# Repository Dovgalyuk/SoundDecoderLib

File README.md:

# Maple RailRoad Sound Decoder

WiFi controller, sound decoder, and sound projects for model trains.

Project includes library for programming the sounds with set of state machines.

There are several ready-to-use sample sound projects.

# Project structure

* esp32 - directory where building of the firmware starts
* hardware - several versions of PCBs for manufacturing the decoder
* projects - ready-to-use sound projects for different locomotives
* compiler - compiler for the sound projects
* emulator - cab emulator for listening sounds with virtual locomotive control
* sample - dummy player which generates wav file by interpreting the sound project
* other directories include the source code of the firmware

# Bringing locomotive to life

* Get the hardware (order PCB, solder the components)
* Build firmware
  * Install ESP32 toolkit (esp idf)
  * Run esp32/build32M.sh (or other version)
* Upload esp32/build32M/esp32sounddecoder.bin into the ESP32 module
* Build selected sound project with compiler/compiler.py
* Upload built project through the web interface into the controller
* Install the controller into the locomotive

# Software features

Controller provides web interface that may be accessed through
WiFi (default address 192.168.4.1).

Sound module plays 8- or 16-bit sounds in 8 channels.

Output functions and sound schemes are programmed with
custom language. The scripts may include conditions,
loops, and finite state machines. These features
may be used for creating complex sound projects.

# Hardware

Controller is intended to be used with G-scale locomotives
with lithium batteries installed, but it may also be used
with track power (some power capacitors are probably needed).

Controller includes the following hardware components:
* ESP32 CPU with embedded WiFi module and flash memory
* Motor driver
* I2S audio power amplifier (MAX98357A)
* 7 programmable outputs
* BEMF for adjusting the motor speed (work in progress)

# Roadmap

* BEMF with new motor driver
* Support of logical input/outputs
* H0-compatible PCB

# Links

* Radio-controlled engines with sound
  - https://github.com/TheDIYGuy999/Rc_Engine_Sound_ESP32
* Cost effective DIY DCC Decoder for model railroad locomotives
  - https://github.com/gab-k/RP2040-Decoder
* NIMRS: open-source NIMRS-21Pin-Decoder, based on the ESP32-S3 microcontroller
  - https://github.com/CDFER/NIMRS-21Pin-Decoder
  - https://github.com/ProjectInitiative/NIMRS-Firmware

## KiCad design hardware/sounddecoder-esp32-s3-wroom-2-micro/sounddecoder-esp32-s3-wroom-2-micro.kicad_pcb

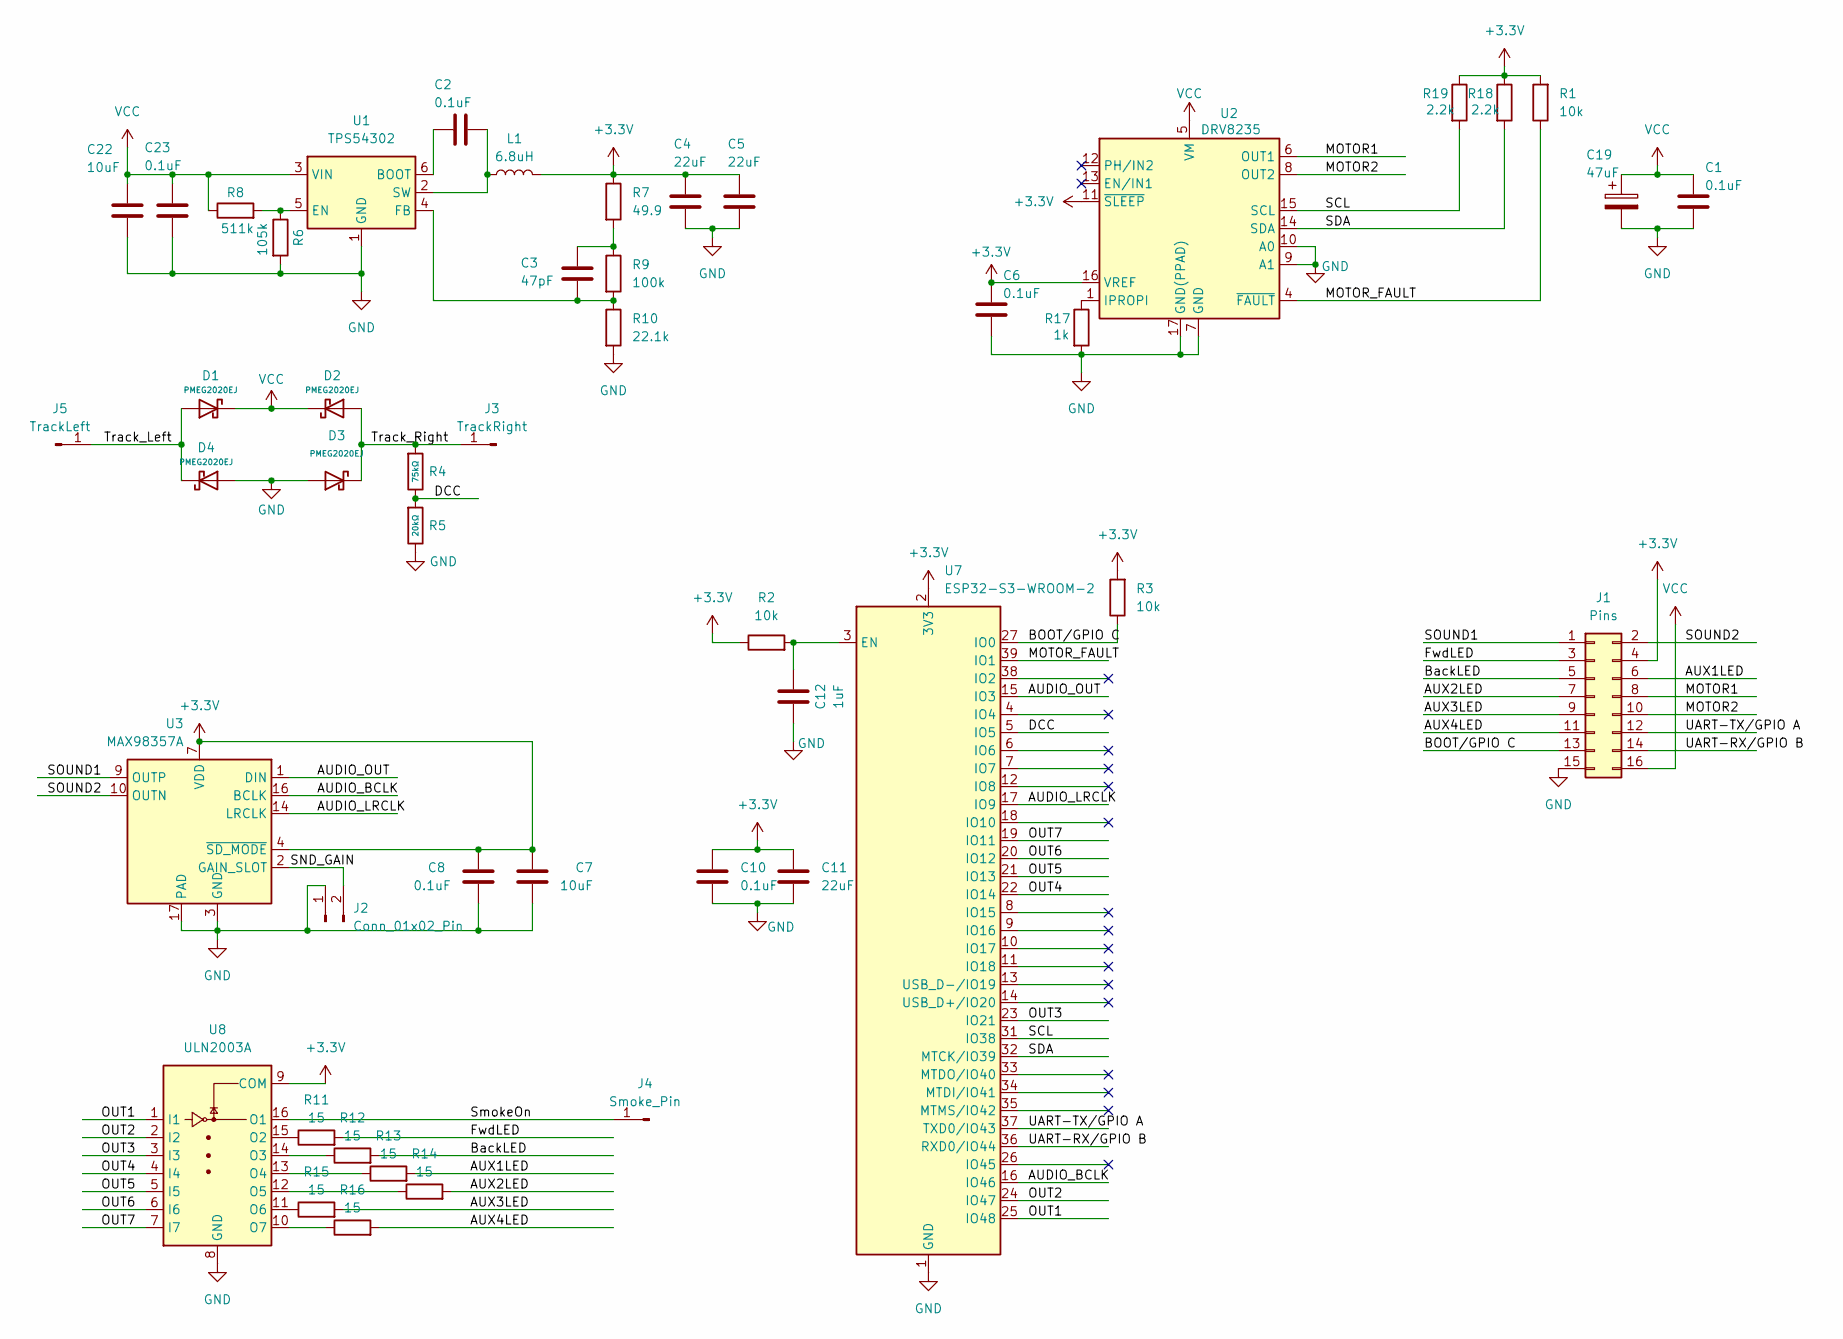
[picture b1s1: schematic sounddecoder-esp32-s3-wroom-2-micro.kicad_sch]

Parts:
C1, C2, C6, C8, C10, C23: 0.1uF; C_0603_1608Metric
C3: 47pF; C_0603_1608Metric
C4, C5, C11: 22uF; C_0603_1608Metric
C7, C22: 10uF; C_0603_1608Metric
C12: 1uF; C_0603_1608Metric
C19: 47uF; CP_Elec_6.3x5.4
D1, D2, D3, D4: PMEG2020EJ; D_SOD-323; Forward Voltage (Vf@If) 450mV@1.0A; Reverse Voltage (Vr) 20V; Part B5817WS; LCSC C7420329
J1: Pins; PinHeader_2x08_P2.00mm_Vertical
J2: Conn_01x02_Pin; SolderJumper-2_P1.3mm_Open_RoundedPad1.0x1.5mm
J3: TrackRight; TestPoint_THTPad_1.0x1.0mm_Drill0.5mm
J4: Smoke_Pin; TestPoint_THTPad_1.0x1.0mm_Drill0.5mm
J5: TrackLeft; TestPoint_THTPad_1.0x1.0mm_Drill0.5mm
L1: 6.8uH; L_Chilisin_BMRA00050530
R1, R2, R3: 10k; C_0603_1608Metric
R4: 75kΩ; C_0603_1608Metric; Overload Voltage (Max) 50V; Tolerance ±1%; Part 0402WGF7502TCE; LCSC C25798
R5: 20kΩ; C_0603_1608Metric; Overload Voltage (Max) 50V; Tolerance ±1%; Part 0402WGF2002TCE; LCSC C25765
R6: 105k; C_0603_1608Metric
R7: 49.9; C_0603_1608Metric
R8: 511k; C_0603_1608Metric
R9: 100k; C_0603_1608Metric
R10: 22.1k; C_0603_1608Metric
R11, R12, R13, R14, R15, R16: 15; C_0603_1608Metric
R17: 1k; C_0603_1608Metric
R18, R19: 2.2k; C_0603_1608Metric
U1: TPS54302; SOT-23-6
U2: DRV8235; WQFN-16-1EP_3x3mm_P0.5mm_EP1.68x1.68mm_ThermalVias
U3: MAX98357A; TQFN-16-1EP_3x3mm_P0.5mm_EP1.23x1.23mm
U7: ESP32-S3-WROOM-2
U8: ULN2003A; SO-16_3.9x9.9mm_P1.27mm

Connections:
+3.3V: C4.1, C5.1, C6.1, C7.1, C8.1, C10.1, C11.1, J1.4, L1.2, R1.2, R2.1, R3.2, R7.1, R18.1, R19.1, U2.11 (~SLEEP), U2.16 (VREF), U3.4 (~SD_MODE), U3.7 (VDD), U3.8 (VDD), U7.2 (3V3), U8.9 (COM)
/AUDIO_BCLK: U3.16 (BCLK), U7.16 (IO46)
/AUDIO_LRCLK: U3.14 (LRCLK), U7.17 (IO9)
/AUDIO_OUT: U3.1 (DIN), U7.15 (IO3)
/AUX1LED: J1.6, R13.2
/AUX2LED: J1.7, R14.2
/AUX3LED: J1.9, R15.2
/AUX4LED: J1.11, R16.2
/BOOT/GPIO C: J1.13, R3.1, U7.27 (IO0)
/BackLED: J1.5, R12.2
/DCC: R4.2, R5.1, U7.5 (IO5)
/FwdLED: J1.3, R11.2
/MOTOR1: J1.8, U2.6 (OUT1)
/MOTOR2: J1.10, U2.8 (OUT2)
/MOTOR_FAULT: R1.1, U2.4 (~FAULT), U7.39 (IO1)
/OUT1: U7.25 (IO48), U8.1 (I1)
/OUT2: U7.24 (IO47), U8.2 (I2)
/OUT3: U7.23 (IO21), U8.3 (I3)
/OUT4: U7.22 (IO14), U8.4 (I4)
/OUT5: U7.21 (IO13), U8.5 (I5)
/OUT6: U7.20 (IO12), U8.6 (I6)
/OUT7: U7.19 (IO11), U8.7 (I7)
/SCL: R19.2, U2.15 (SCL), U7.31 (IO38)
/SDA: R18.2, U2.14 (SDA), U7.32 (MTCK/IO39)
/SND_GAIN: J2.2, U3.2 (GAIN_SLOT)
/SOUND1: J1.1, U3.9 (OUTP)
/SOUND2: J1.2, U3.10 (OUTN)
/SmokeOn: J4.1, U8.16 (O1)
/Track_Left: D1.2, D4.1, J5.1
/Track_Right: D2.2, D3.1, J3.1, R4.1
/UART-RX/GPIO B: J1.14, U7.36 (RXD0/IO44)
/UART-TX/GPIO A: J1.12, U7.37 (TXD0/IO43)
GND: C1.2, C4.2, C5.2, C6.2, C7.2, C8.2, C10.2, C11.2, C12.1, C19.2, C22.2, C23.2, D3.2, D4.2, J1.15, J2.1, R5.2, R6.2, R10.2, R17.2, U1.1 (GND), U2.7 (GND), U2.9 (A1), U2.10 (A0), U2.17 (GND(PPAD)), U3.3 (GND), U3.11 (GND), U3.15 (GND), U3.17 (PAD), U7.1 (GND), U7.40 (GND), U7.41 (GND), U8.8 (GND)
unnamed: C3.1, R7.2, R9.1
unnamed: C2.1, U1.6 (BOOT)
unnamed: R6.1, R8.2, U1.5 (EN)
unnamed: C3.2, R9.2, R10.1, U1.4 (FB)
unnamed: C2.2, L1.1, U1.2 (SW)
unnamed: R17.1, U2.1 (IPROPI)
unnamed: C12.2, R2.2, U7.3 (EN)
unnamed: R11.1, U8.15 (O2)
unnamed: R12.1, U8.14 (O3)
unnamed: R13.1, U8.13 (O4)
unnamed: R14.1, U8.12 (O5)
unnamed: R15.1, U8.11 (O6)
unnamed: R16.1, U8.10 (O7)
VCC: C1.1, C19.1, C22.1, C23.1, D1.1, D2.1, J1.16, R8.1, U1.3 (VIN), U2.5 (VM)

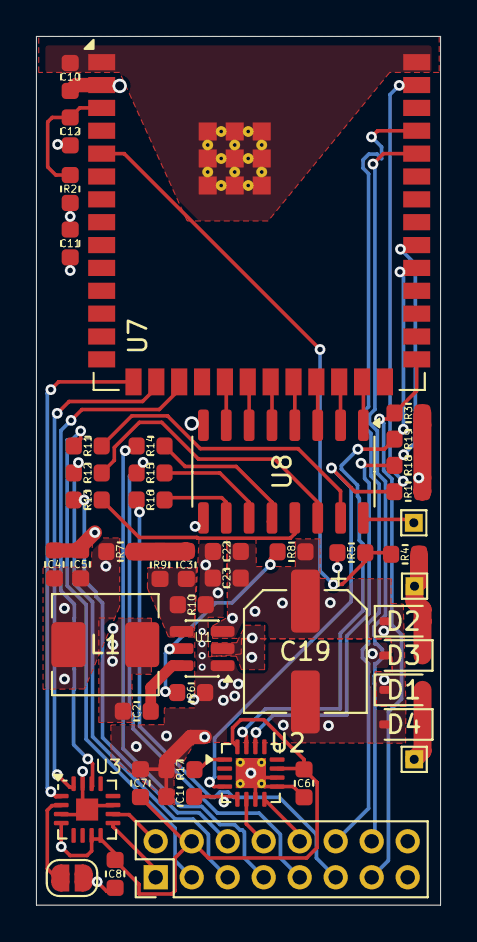
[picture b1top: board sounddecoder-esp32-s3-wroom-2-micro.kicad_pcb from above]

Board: 4 copper layers, 22.5 x 48.3 mm, 48 parts (0 on the bottom side), 47 nets.

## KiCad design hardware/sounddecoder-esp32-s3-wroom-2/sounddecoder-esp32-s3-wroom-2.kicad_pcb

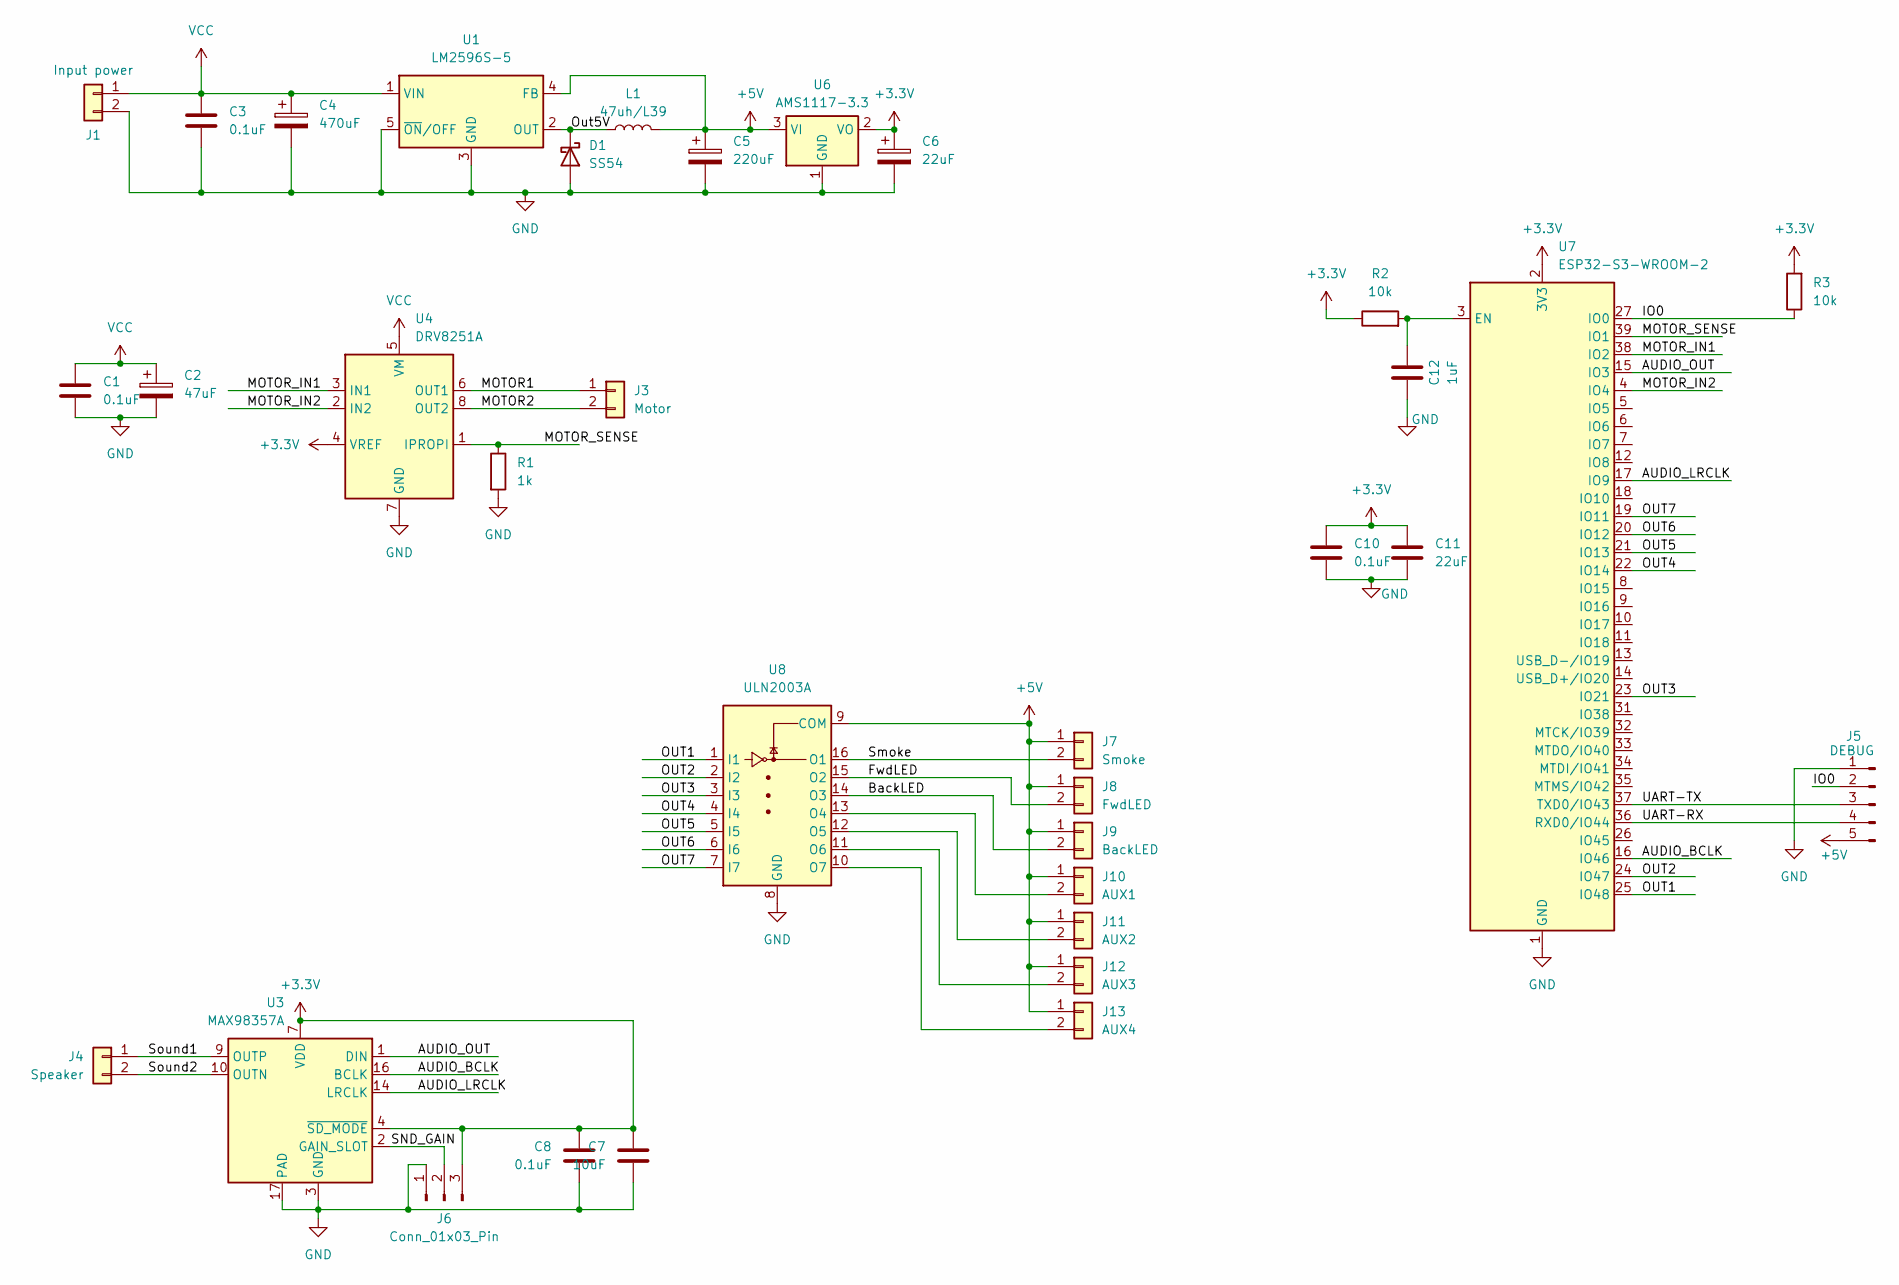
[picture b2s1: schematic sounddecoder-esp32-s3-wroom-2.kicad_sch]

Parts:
C1, C3, C8, C10: 0.1uF; C_0805_2012Metric_Pad1.18x1.45mm_HandSolder
C2: 47uF; CP_Elec_6.3x5.4
C4: 470uF; CP_Elec_10x10.5
C5: 220uF; C_Elec_6.3x7.7
C6: 22uF; CP_Elec_4x5.4
C7: 10uF; C_0805_2012Metric_Pad1.18x1.45mm_HandSolder
C11: 22uF; C_0805_2012Metric_Pad1.18x1.45mm_HandSolder
C12: 1uF; C_0805_2012Metric_Pad1.18x1.45mm_HandSolder
D1: SS54; D_SMC
J1: Input power; TerminalBlock_Xinya_XY308-2.54-2P_1x02_P2.54mm_Horizontal
J3: Motor; TerminalBlock_Xinya_XY308-2.54-2P_1x02_P2.54mm_Horizontal
J4: Speaker; TerminalBlock_Xinya_XY308-2.54-2P_1x02_P2.54mm_Horizontal
J5: DEBUG; PinHeader_1x05_P2.54mm_Horizontal
J6: Conn_01x03_Pin; PinHeader_1x03_P1.00mm_Vertical
J7: Smoke; TerminalBlock_Xinya_XY308-2.54-2P_1x02_P2.54mm_Horizontal
J8: FwdLED; TerminalBlock_Xinya_XY308-2.54-2P_1x02_P2.54mm_Horizontal
J9: BackLED; TerminalBlock_Xinya_XY308-2.54-2P_1x02_P2.54mm_Horizontal
J10: AUX1; TerminalBlock_Xinya_XY308-2.54-2P_1x02_P2.54mm_Horizontal
J11: AUX2; TerminalBlock_Xinya_XY308-2.54-2P_1x02_P2.54mm_Horizontal
J12: AUX3; TerminalBlock_Xinya_XY308-2.54-2P_1x02_P2.54mm_Horizontal
J13: AUX4; TerminalBlock_Xinya_XY308-2.54-2P_1x02_P2.54mm_Horizontal
L1: 47uh/L39; L_Bourns_SRP1245A
R1: 1k; R_0805_2012Metric_Pad1.20x1.40mm_HandSolder
R2, R3: 10k; R_0805_2012Metric_Pad1.20x1.40mm_HandSolder
U1: LM2596S-5; TO-263-5_TabPin3
U3: MAX98357A; TQFN-16-1EP_3x3mm_P0.5mm_EP1.23x1.23mm
U4: DRV8251A; Texas_HSOP-8-1EP_3.9x4.9mm_P1.27mm_ThermalVias
U6: AMS1117-3.3; SOT-223-3_TabPin2
U7: ESP32-S3-WROOM-2
U8: ULN2003A; SO-16_3.9x9.9mm_P1.27mm

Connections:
+3.3V: C6.1, C7.1, C8.1, C10.1, C11.1, J6.3, R2.1, R3.2, U3.4 (~SD_MODE), U3.7 (VDD), U3.8 (VDD), U4.4 (VREF), U6.2 (VO), U7.2 (3V3)
+5V: C5.1, J5.5, J7.1, J8.1, J9.1, J10.1, J11.1, J12.1, J13.1, L1.2, U1.4 (FB), U6.3 (VI), U8.9 (COM)
/AUDIO_BCLK: U3.16 (BCLK), U7.16 (IO46)
/AUDIO_LRCLK: U3.14 (LRCLK), U7.17 (IO9)
/AUDIO_OUT: U3.1 (DIN), U7.15 (IO3)
/BackLED: J9.2, U8.14 (O3)
/FwdLED: J8.2, U8.15 (O2)
/IO0: J5.2, R3.1, U7.27 (IO0)
/MOTOR1: J3.1, U4.6 (OUT1)
/MOTOR2: J3.2, U4.8 (OUT2)
/MOTOR_IN1: U4.3 (IN1), U7.38 (IO2)
/MOTOR_IN2: U4.2 (IN2), U7.4 (IO4)
/MOTOR_SENSE: R1.1, U4.1 (IPROPI), U7.39 (IO1)
/OUT1: U7.25 (IO48), U8.1 (I1)
/OUT2: U7.24 (IO47), U8.2 (I2)
/OUT3: U7.23 (IO21), U8.3 (I3)
/OUT4: U7.22 (IO14), U8.4 (I4)
/OUT5: U7.21 (IO13), U8.5 (I5)
/OUT6: U7.20 (IO12), U8.6 (I6)
/OUT7: U7.19 (IO11), U8.7 (I7)
/Out5V: D1.1 (K), L1.1, U1.2 (OUT)
/SND_GAIN: J6.2, U3.2 (GAIN_SLOT)
/Smoke: J7.2, U8.16 (O1)
/Sound1: J4.1, U3.9 (OUTP)
/Sound2: J4.2, U3.10 (OUTN)
/UART-RX: J5.4, U7.36 (RXD0/IO44)
/UART-TX: J5.3, U7.37 (TXD0/IO43)
GND: C1.2, C2.2, C3.2, C4.2, C5.2, C6.2, C7.2, C8.2, C10.2, C11.2, C12.1, D1.2 (A), J1.2, J5.1, J6.1, R1.2, U1.3 (GND), U1.5 (~ON/OFF), U3.3 (GND), U3.11 (GND), U3.15 (GND), U3.17 (PAD), U4.7 (GND), U4.9 (GND), U6.1 (GND), U7.1 (GND), U7.40 (GND), U7.41 (GND), U8.8 (GND)
unnamed: J10.2, U8.13 (O4)
unnamed: J11.2, U8.12 (O5)
unnamed: J12.2, U8.11 (O6)
unnamed: J13.2, U8.10 (O7)
unnamed: C12.2, R2.2, U7.3 (EN)
VCC: C1.1, C2.1, C3.1, C4.1, J1.1, U1.1 (VIN), U4.5 (VM)

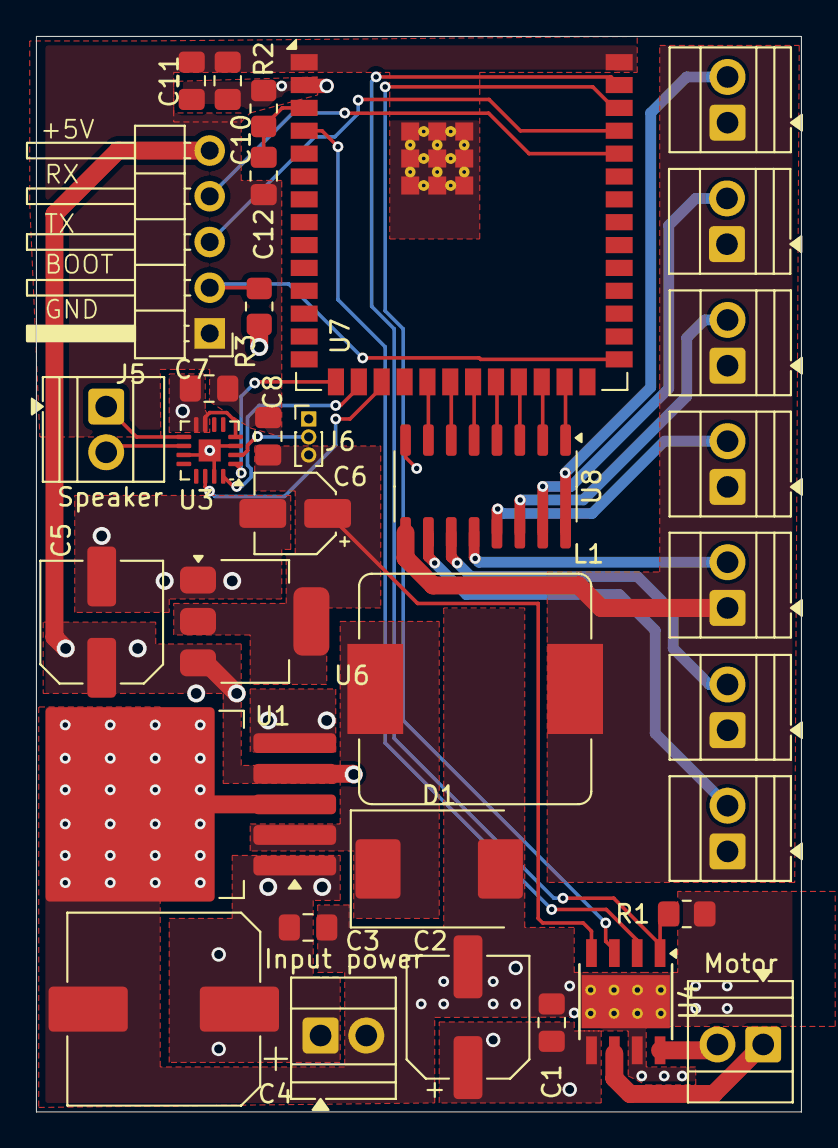
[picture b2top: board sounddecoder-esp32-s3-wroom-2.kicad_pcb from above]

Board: 4 copper layers, 42.5 x 59.8 mm, 34 parts (0 on the bottom side), 34 nets.

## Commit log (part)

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2026-02-18 Added links
2026-02-18 Fixed list
2026-02-18 One more list fix
2026-02-18 first working version
2026-02-19 Update LICENSE
2026-02-19 Added VM and Player abstractions.
2026-03-02 fix for github actions
2026-03-04 Almost working web interface
2026-03-09 Update for new project bytecode
2026-03-09 Running locomotive
2026-03-11 Implemented external flash support
2026-03-12 Upload datasheets and create schematic stub
2026-03-16 Many updates
2026-03-23 Created PCB
2026-04-16 Started working on board v2
2026-04-16 Project cleanup
2026-04-21 Finished v2 board
2026-04-23 Updated physical outputs support
2026-04-26 Implemented physical output parameters
2026-04-28 Refactoring storage of the physical outputs
